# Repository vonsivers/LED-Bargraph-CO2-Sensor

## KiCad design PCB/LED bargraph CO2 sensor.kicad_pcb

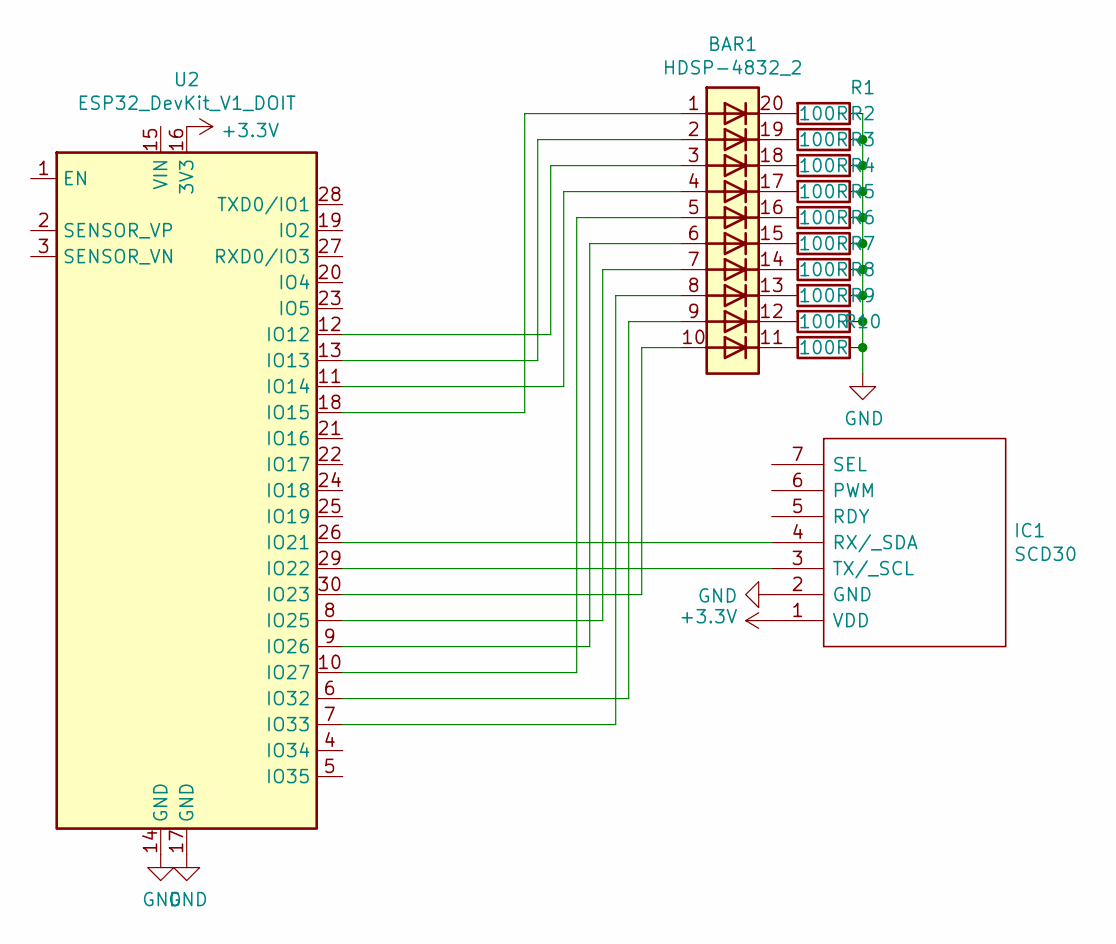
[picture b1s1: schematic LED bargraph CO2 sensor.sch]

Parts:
BAR1: HDSP-4832_2; HDSP-4832
IC1: SCD30; Mouser Part Number 403-SCD30
R1, R2, R3, R4, R5, R6, R7, R8, R9, R10: 100R; R_0805_2012Metric_Pad1.15x1.40mm_HandSolder
U2: ESP32_DevKit_V1_DOIT; esp32_devkit_v1_doit

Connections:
+3V3: IC1.1 (VDD), U2.16 (3V3)
GND: IC1.2 (GND), R1.1, R2.1, R3.1, R4.1, R5.1, R6.1, R7.1, R8.1, R9.1, R10.1, U2.14 (GND), U2.17 (GND)
unnamed: BAR1.1 (A), U2.18 (IO15)
unnamed: BAR1.2 (A), U2.13 (IO13)
unnamed: BAR1.3 (A), U2.12 (IO12)
unnamed: BAR1.4 (A), U2.11 (IO14)
unnamed: BAR1.5 (A), U2.10 (IO27)
unnamed: BAR1.6 (A), U2.9 (IO26)
unnamed: BAR1.7 (A), U2.8 (IO25)
unnamed: BAR1.8 (A), U2.7 (IO33)
unnamed: BAR1.9 (A), U2.6 (IO32)
unnamed: BAR1.10 (A), U2.30 (IO23)
unnamed: BAR1.11 (K), R10.2
unnamed: BAR1.12 (K), R9.2
unnamed: BAR1.13 (K), R8.2
unnamed: BAR1.14 (K), R7.2
unnamed: BAR1.15 (K), R6.2
unnamed: BAR1.16 (K), R5.2
unnamed: BAR1.17 (K), R4.2
unnamed: BAR1.18 (K), R3.2
unnamed: BAR1.19 (K), R2.2
unnamed: BAR1.20 (K), R1.2
unnamed: IC1.3 (TX/_SCL), U2.29 (IO22)
unnamed: IC1.4 (RX/_SDA), U2.26 (IO21)

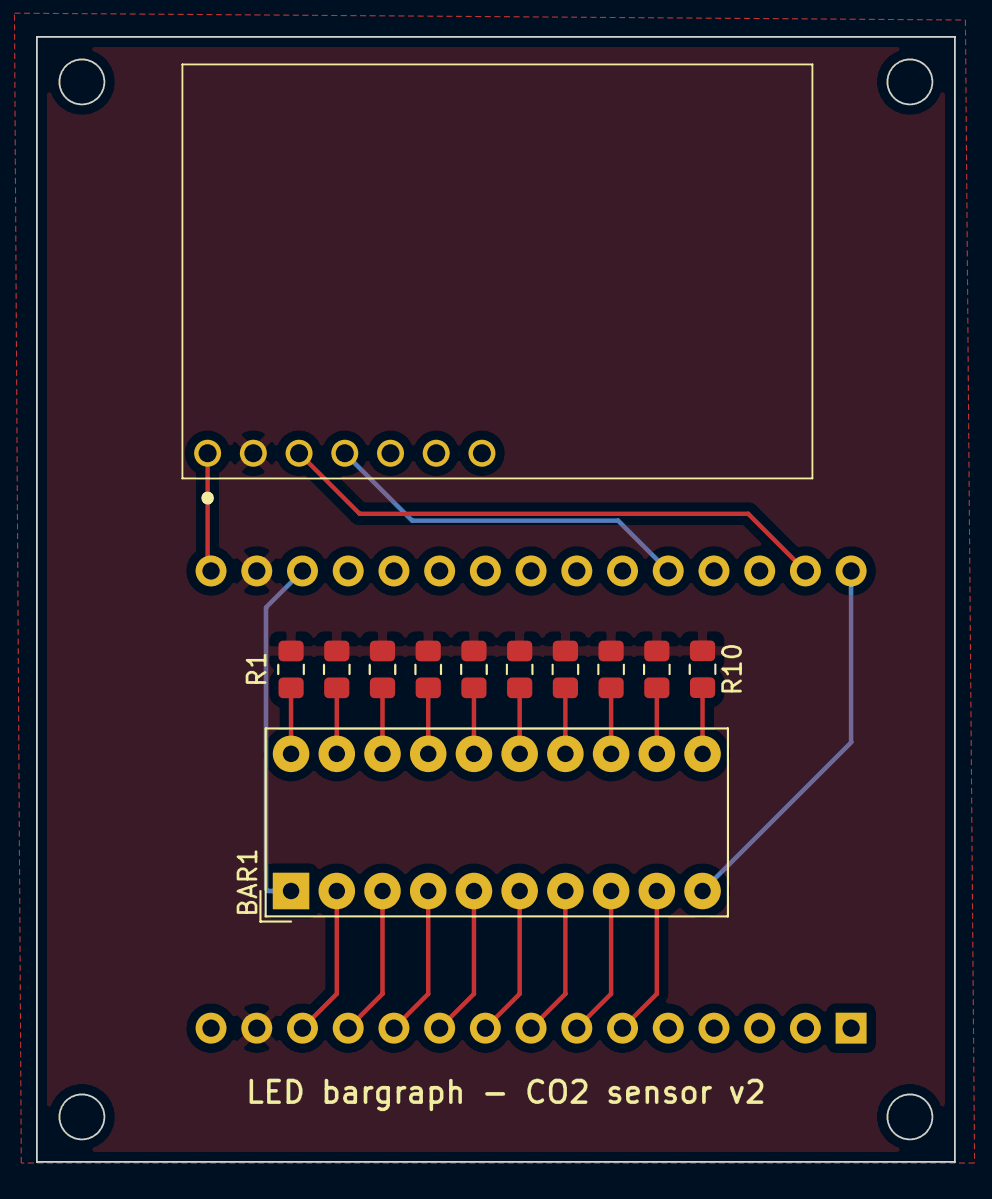
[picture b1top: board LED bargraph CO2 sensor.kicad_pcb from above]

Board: 2 copper layers, 51.0 x 62.5 mm, 13 parts (1 on the bottom side), 24 nets.

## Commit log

2021-05-23 added PCB images
